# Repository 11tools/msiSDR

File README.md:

this is an Software Define Radio receiver PCB project base on msi2500 and msi001. use kicad to view it

这是一个基于msi2500 和 msi001的软件无线电PCB工程项目， 使用kiCAD浏览此工程

如果需要PCB打样，把gerber目录下的文件发给PCB加工厂即可

Send gerbar files to PCB factory . you'd better to use SMT

建议叫工厂SMT贴片，手动焊接容易太多bug

软件使用SDRuno（选SDRPlay）

software compatible with SDRplay

使用效果

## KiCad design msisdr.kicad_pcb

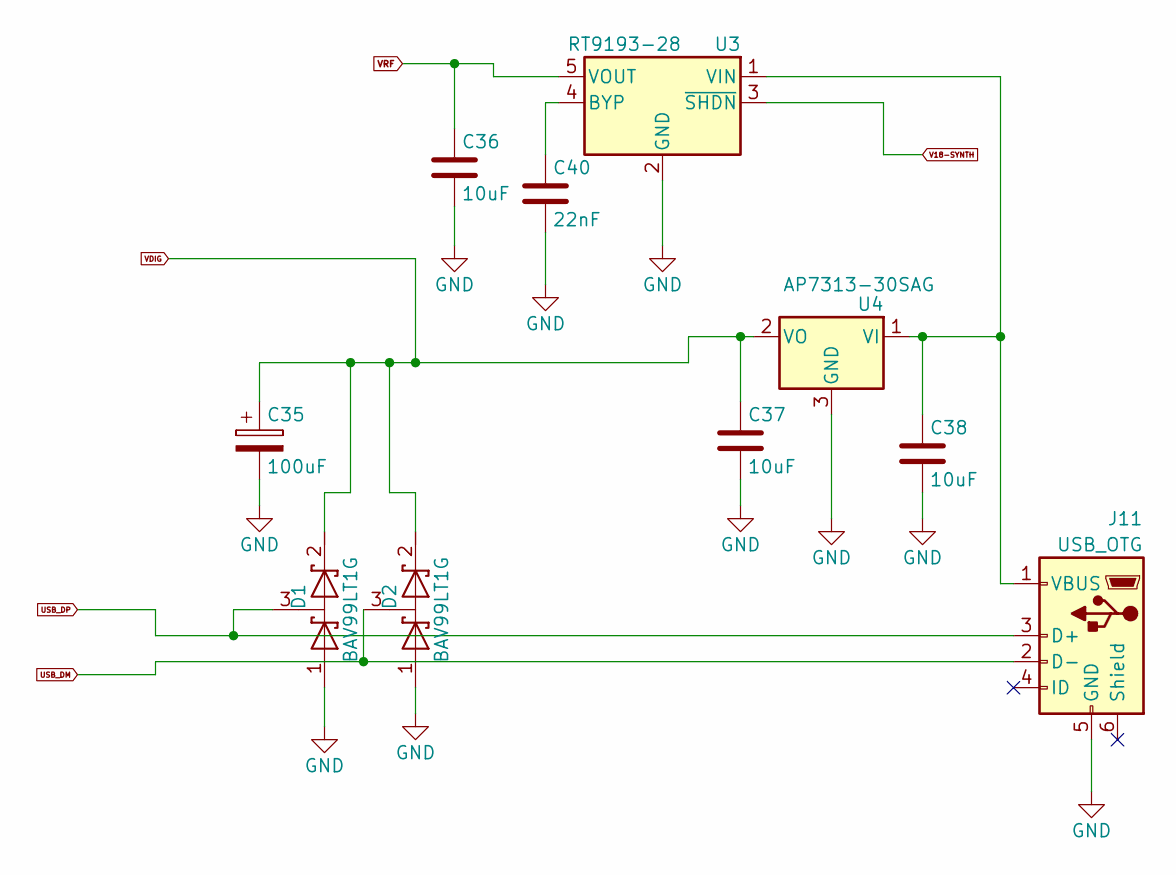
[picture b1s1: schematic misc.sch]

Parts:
C35: 100uF; CP_Radial_D5.0mm_P2.50mm
C36, C37, C38: 10uF; C_0805
C40: 22nF; C_0603
D1, D2: BAV99LT1G; SOT-23
J11: USB_OTG; USB_Mini-B
U3: RT9193-28; SOT-23-5
U4: AP7313-30SAG; SOT-23

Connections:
GND: C35.2, C36.2, C37.2, C38.2, C40.2, D1.1 (A), D2.1 (A), J11.5 (GND), U3.2 (GND), U4.3 (GND); also elsewhere on the board
unnamed: C38.1, J11.1 (VBUS), U3.1 (VIN), U4.1 (VI)
unnamed: C40.1, U3.4 (BYP)
USB_DM: D2.3 (common), J11.2 (D-); also elsewhere on the board
USB_DP: D1.3 (common), J11.3 (D+); also elsewhere on the board
V18-SYNTH: U3.3 (~SHDN~); also elsewhere on the board
VDIG: C35.1, C37.1, D1.2 (K), D2.2 (K), U4.2 (VO); also elsewhere on the board
VRF: C36.1, U3.5 (VOUT); also elsewhere on the board

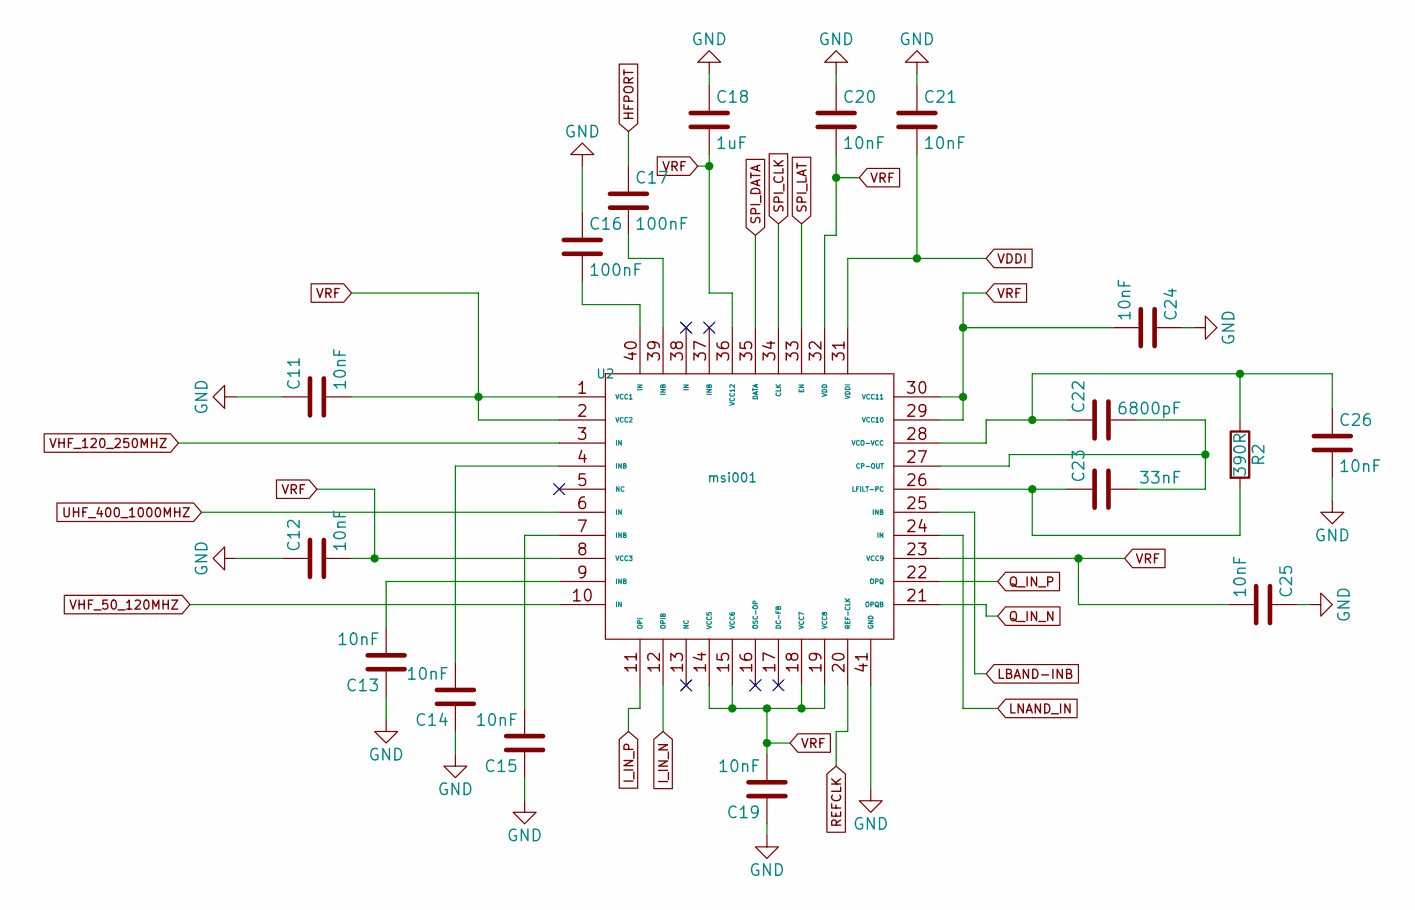
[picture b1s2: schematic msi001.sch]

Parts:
C11, C12, C13, C14, C15, C19, C20, C21, C24, C25, C26: 10nF; C_0603
C16, C17: 100nF; C_0603
C18: 1uF; C_0805
C22: 6800pF; C_0603
C23: 33nF; C_0603
R2: 390R; R_0603
U2: msi001; QFN-40-1EP_6x6mm_Pitch0.5mm

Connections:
GND: C11.1, C12.1, C13.1, C14.1, C15.1, C16.1, C18.1, C19.1, C20.1, C21.1, C24.1, C25.1, C26.2, U2.41 (GND); also elsewhere on the board
HFPORT: C17.1; also elsewhere on the board
I_IN_N: U2.12 (OPIB); also elsewhere on the board
I_IN_P: U2.11 (OPI); also elsewhere on the board
LBAND-INB: U2.25 (INB)
LNAND_IN: U2.24 (IN)
unnamed: C13.2, U2.9 (INB)
unnamed: C14.2, U2.4 (INB)
unnamed: C15.2, U2.7 (INB)
unnamed: C16.2, U2.40 (IN)
unnamed: C17.2, U2.39 (INB)
unnamed: C22.1, C26.1, R2.1, U2.28 (VCO-VCC)
unnamed: C22.2, C23.2, U2.27 (CP-OUT)
unnamed: C23.1, R2.2, U2.26 (LFILT-PC)
Q_IN_N: U2.21 (OPQB); also elsewhere on the board
Q_IN_P: U2.22 (OPQ); also elsewhere on the board
REFCLK: U2.20 (REF-CLK); also elsewhere on the board
SPI_CLK: U2.34 (CLK); also elsewhere on the board
SPI_DATA: U2.35 (DATA); also elsewhere on the board
SPI_LAT: U2.33 (EN); also elsewhere on the board
UHF_400_1000MHZ: U2.6 (IN); also elsewhere on the board
VDDI: C21.2, U2.31 (VDDI); also elsewhere on the board
VHF_50_120MHZ: U2.10 (IN); also elsewhere on the board
VHF_120_250MHZ: U2.3 (IN); also elsewhere on the board
VRF: C11.2, C12.2, C18.2, C19.2, C20.2, C24.2, C25.2, U2.1 (VCC1), U2.2 (VCC2), U2.8 (VCC3), U2.14 (VCC5), U2.15 (VCC6), U2.18 (VCC7), U2.19 (VCC8), U2.23 (VCC9), U2.29 (VCC10), U2.30 (VCC11), U2.32 (VDD), U2.36 (VCC12); also elsewhere on the board

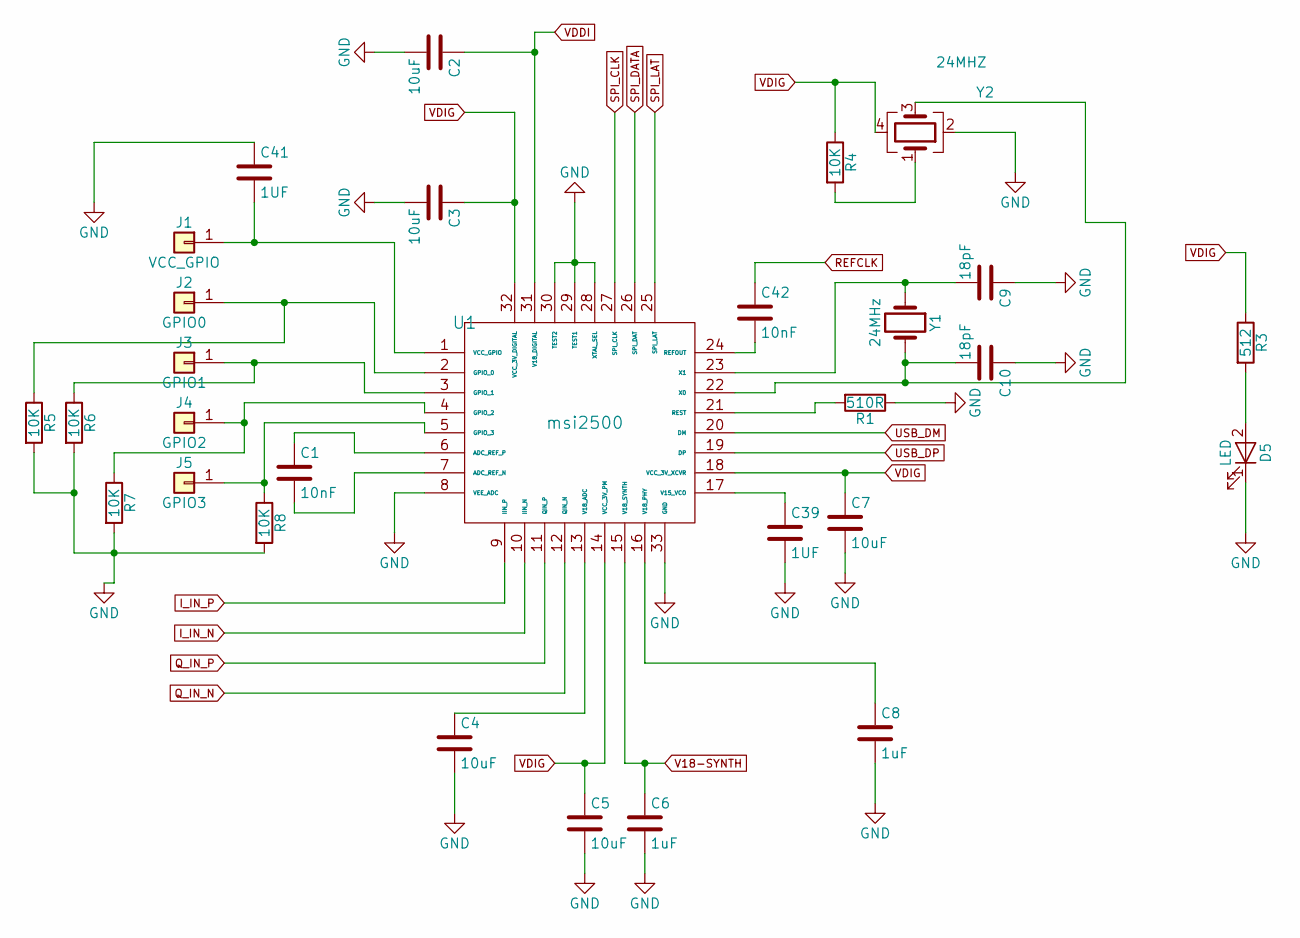
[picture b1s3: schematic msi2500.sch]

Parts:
C1, C42: 10nF; C_0603
C2, C3, C4, C5, C7: 10uF; C_0805
C6, C8: 1uF; C_0805
C9, C10: 18pF; C_0603
C39, C41: 1UF; C_0805
D5: LED; D_DO-35_SOD27_P2.54mm_Vertical_AnodeUp
J1: VCC_GPIO; Pin_d0.7mm_L6.5mm_W1.8mm_FlatFork
J2: GPIO0; Pin_d0.7mm_L6.5mm_W1.8mm_FlatFork
J3: GPIO1; Pin_d0.7mm_L6.5mm_W1.8mm_FlatFork
J4: GPIO2; Pin_d0.7mm_L6.5mm_W1.8mm_FlatFork
J5: GPIO3; Pin_d0.7mm_L6.5mm_W1.8mm_FlatFork
R1: 510R; R_0603
R3: 512; R_0603
R4, R5, R6, R7, R8: 10K; R_0603
U1: msi2500; QFN-32-1EP_5x5mm_Pitch0.5mm
Y1: 24MHz; Crystal_HC50_Vertical
Y2: 24MHZ; Crystal_SMD_7050-4pin_7.0x5.0mm

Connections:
GND: C2.2, C3.2, C4.2, C5.2, C6.2, C7.2, C8.2, C9.1, C10.1, C39.2, C41.1, D5.1 (K), R1.1, R5.2, R6.2, R7.2, R8.2, U1.8 (VEE_ADC), U1.28 (XTAL_SEL), U1.29 (TEST1), U1.30 (TEST2), U1.33 (GND), Y2.2; also elsewhere on the board
I_IN_N: U1.10 (IIN_N); also elsewhere on the board
I_IN_P: U1.9 (IIN_P); also elsewhere on the board
unnamed: C1.1, U1.6 (ADC_REF_P)
unnamed: C1.2, U1.7 (ADC_REF_N)
unnamed: C4.1, U1.13 (V18_ADC)
unnamed: C8.1, U1.16 (V18_PHY)
unnamed: C9.2, U1.23 (X1), Y1.1
unnamed: C10.2, U1.22 (X0), Y1.2, Y2.3
unnamed: C39.1, U1.17 (V15_VCO)
unnamed: C41.2, J1.1, U1.1 (VCC_GPIO)
unnamed: C42.2, U1.24 (REFOUT)
unnamed: D5.2 (A), R3.2
unnamed: J2.1, R5.1, U1.2 (GPIO_0)
unnamed: J3.1, R6.1, U1.3 (GPIO_1)
unnamed: J4.1, R7.1, U1.4 (GPIO_2)
unnamed: J5.1, R8.1, U1.5 (GPIO_3)
unnamed: R1.2, U1.21 (REST)
unnamed: R4.2, Y2.1
Q_IN_N: U1.12 (QIN_N); also elsewhere on the board
Q_IN_P: U1.11 (QIN_P); also elsewhere on the board
REFCLK: C42.1; also elsewhere on the board
SPI_CLK: U1.27 (SPI_CLK); also elsewhere on the board
SPI_DATA: U1.26 (SPI_DAT); also elsewhere on the board
SPI_LAT: U1.25 (SPI_LAT); also elsewhere on the board
USB_DM: U1.20 (DM); also elsewhere on the board
USB_DP: U1.19 (DP); also elsewhere on the board
V18-SYNTH: C6.1, U1.15 (V18_SYNTH); also elsewhere on the board
VDDI: C2.1, U1.31 (V18_DIGITAL); also elsewhere on the board
VDIG: C3.1, C5.1, C7.1, R3.1, R4.1, U1.14 (VCC_3V_PM), U1.18 (VCC_3V_XCVR), U1.32 (VCC_3V_DIGITAL), Y2.4; also elsewhere on the board

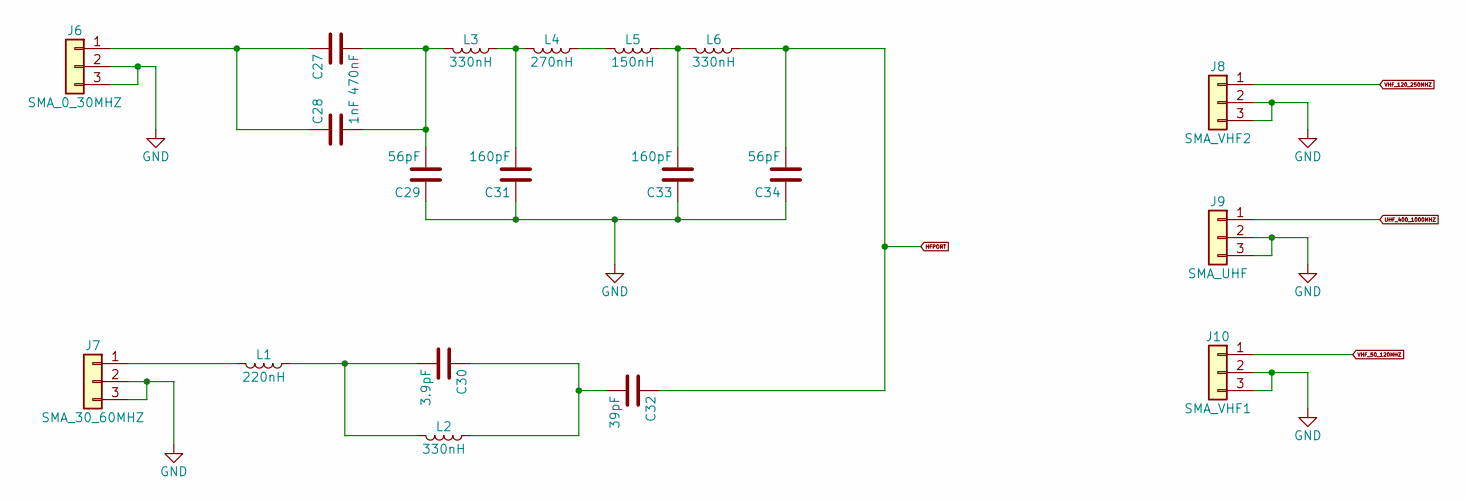
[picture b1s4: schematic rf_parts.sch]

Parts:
C27: 470nF; C_0805
C28: 1nF; C_0603
C29, C34: 56pF; C_0603
C30: 3.9pF; C_0603
C31, C33: 160pF; C_0603
C32: 39pF; C_0603
J6: SMA_0_30MHZ; SMA_OPL_EM
J7: SMA_30_60MHZ; SMA_OPL_EM
J8: SMA_VHF2; SMA_OPL_EMPTYHEAD
J9: SMA_UHF; SMA_OPL_EMPTYHEAD
J10: SMA_VHF1; SMA_OPL_EMPTYHEAD
L1: 220nH; L_0805
L2, L3, L6: 330nH; L_0805
L4: 270nH; L_0805
L5: 150nH; L_0805

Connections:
GND: C29.1, C31.1, C33.1, C34.1, J6.2, J6.3, J7.2, J7.3, J8.2, J8.3, J9.2, J9.3, J10.2, J10.3; also elsewhere on the board
HFPORT: C32.1, C34.2, L6.1; also elsewhere on the board
unnamed: C27.1, C28.1, J6.1
unnamed: C27.2, C28.2, C29.2, L3.2
unnamed: C30.1, C32.2, L2.1
unnamed: C30.2, L1.1, L2.2
unnamed: C31.2, L3.1, L4.2
unnamed: C33.2, L5.1, L6.2
unnamed: J7.1, L1.2
unnamed: L4.1, L5.2
UHF_400_1000MHZ: J9.1; also elsewhere on the board
VHF_50_120MHZ: J10.1; also elsewhere on the board
VHF_120_250MHZ: J8.1; also elsewhere on the board

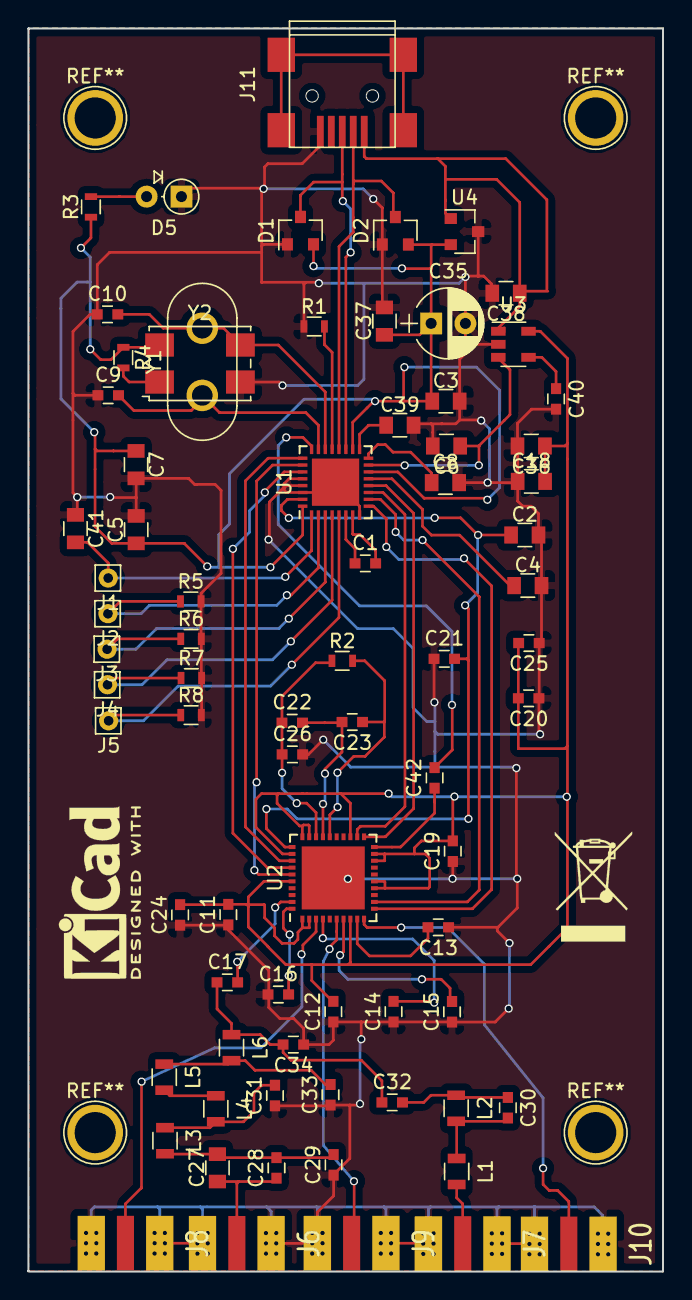
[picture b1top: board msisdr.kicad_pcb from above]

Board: 2 copper layers, 46.3 x 90.7 mm, 76 parts (0 on the bottom side), 53 nets.

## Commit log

2019-02-17 init msisdr sch
2019-02-17 msi2500 full pcb design
2019-02-17 add readme
2019-02-18 update and fix bug
2019-02-19 update pcb
2019-02-21 finish pcb v1
2019-02-22 add machine hole
2019-02-22 finish drc
2019-02-22 adjust some line and hole
2019-02-22 finally version of pcb
2019-02-23 add gerber file
2019-02-25 change ldo to ap2204r
2019-04-07 use external oscillator repace xtal and add a led
2019-04-13 replace ldo and finish osc pcb layout
2019-04-17 fix oscillator connect to x1 error
2019-04-21 use bav99 replace diode
2019-04-25 add gpio pull down res
2019-05-02 pcb version 2
2019-05-02 add GPL 3.0 license
2019-05-08 fix bugs 1. not connect msi001 4 vcc to VRF 2. msi2500 VCC_GPIO connect to 1uF to GND 3. REF_CLK should use 10nF connect
2019-05-08 finish route and output gerber file
